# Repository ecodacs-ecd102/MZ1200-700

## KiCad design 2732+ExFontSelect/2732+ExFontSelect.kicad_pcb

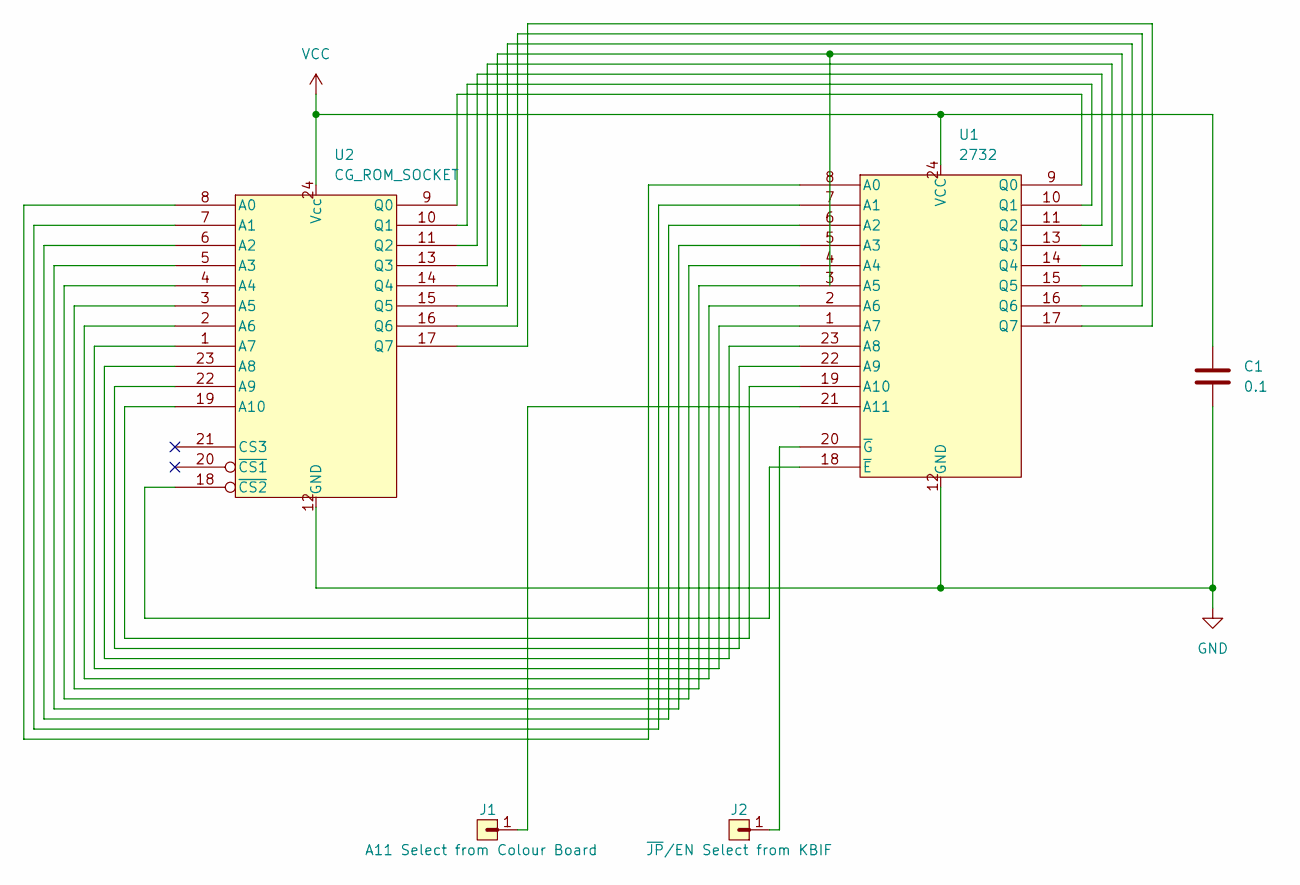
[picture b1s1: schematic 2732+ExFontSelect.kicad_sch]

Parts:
C1: 0.1; LargePad_R_Axial_DIN0204_L3.6mm_D1.6mm_P2.54mm_Vertical
J1: A11 Select from Colour Board; PinHeader_1x01_P2.54mm_Vertical
J2: ~{JP}/EN Select from KBIF; PinHeader_1x01_P2.54mm_Vertical
U1: 2732; DIP-24_W15.24mm_Socket_LongPads
U2: CG_ROM_SOCKET; DIP-24_W15.24mm_Socket_LongPads

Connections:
GND: C1.2, U1.12 (GND), U2.12 (GND)
unnamed: U1.8 (A0), U2.8 (A0)
unnamed: U1.7 (A1), U2.7 (A1)
unnamed: U1.6 (A2), U2.6 (A2)
unnamed: U1.5 (A3), U2.5 (A3)
unnamed: U1.4 (A4), U2.4 (A4)
unnamed: U1.3 (A5), U2.3 (A5)
unnamed: U1.2 (A6), U2.2 (A6)
unnamed: U1.1 (A7), U2.1 (A7)
unnamed: U1.23 (A8), U2.23 (A8)
unnamed: U1.22 (A9), U2.22 (A9)
unnamed: U1.19 (A10), U2.19 (A10)
unnamed: J1.1, U1.21 (A11)
unnamed: U1.9 (Q0), U2.9 (Q0)
unnamed: U1.10 (Q1), U2.10 (Q1)
unnamed: U1.11 (Q2), U2.11 (Q2)
unnamed: U1.13 (Q3), U2.13 (Q3)
unnamed: U1.14 (Q4), U2.14 (Q4)
unnamed: U1.15 (Q5), U2.15 (Q5)
unnamed: U1.16 (Q6), U2.16 (Q6)
unnamed: U1.17 (Q7), U2.17 (Q7)
unnamed: U1.18 (~E), U2.18 (~CS2)
unnamed: J2.1, U1.20 (~G)
VCC: C1.1, U1.24 (VCC), U2.24 (Vcc)

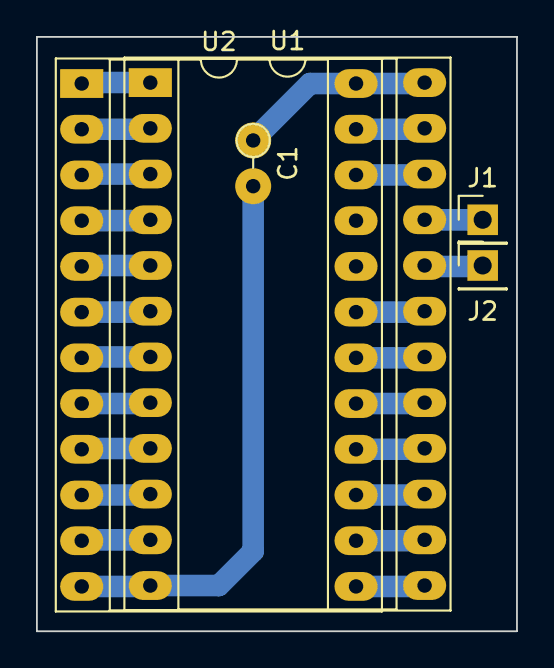
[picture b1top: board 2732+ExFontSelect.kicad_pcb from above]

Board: 2 copper layers, 26.7 x 33.0 mm, 5 parts (0 on the bottom side), 24 nets.
